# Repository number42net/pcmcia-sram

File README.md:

# PCMCIA SRAM board

This board is primarily designed for use in the Amstrad NC-100 and NC-200 portable computers, but will likely work in other computers as well.

## Specifications:
+ 1024K * 8 bits static RAM
+ CR2032 backup battery
+ Long battery life expected, but not yet tested

## Potential issues
+ This project has not yet been fully tested! **Build it at your own risk!**
+ Will likely not work in computers that expect a 16bit card, but this hasn't been tested
+ Currently no write protect switch

## Design
+ This product is Open Source, licensed under [CERN-OHL-P v2](https://ohwr.org/cern_ohl_p_v2.txt)
+ The schematics and PCB designs have been produced with KiCAD 6.0

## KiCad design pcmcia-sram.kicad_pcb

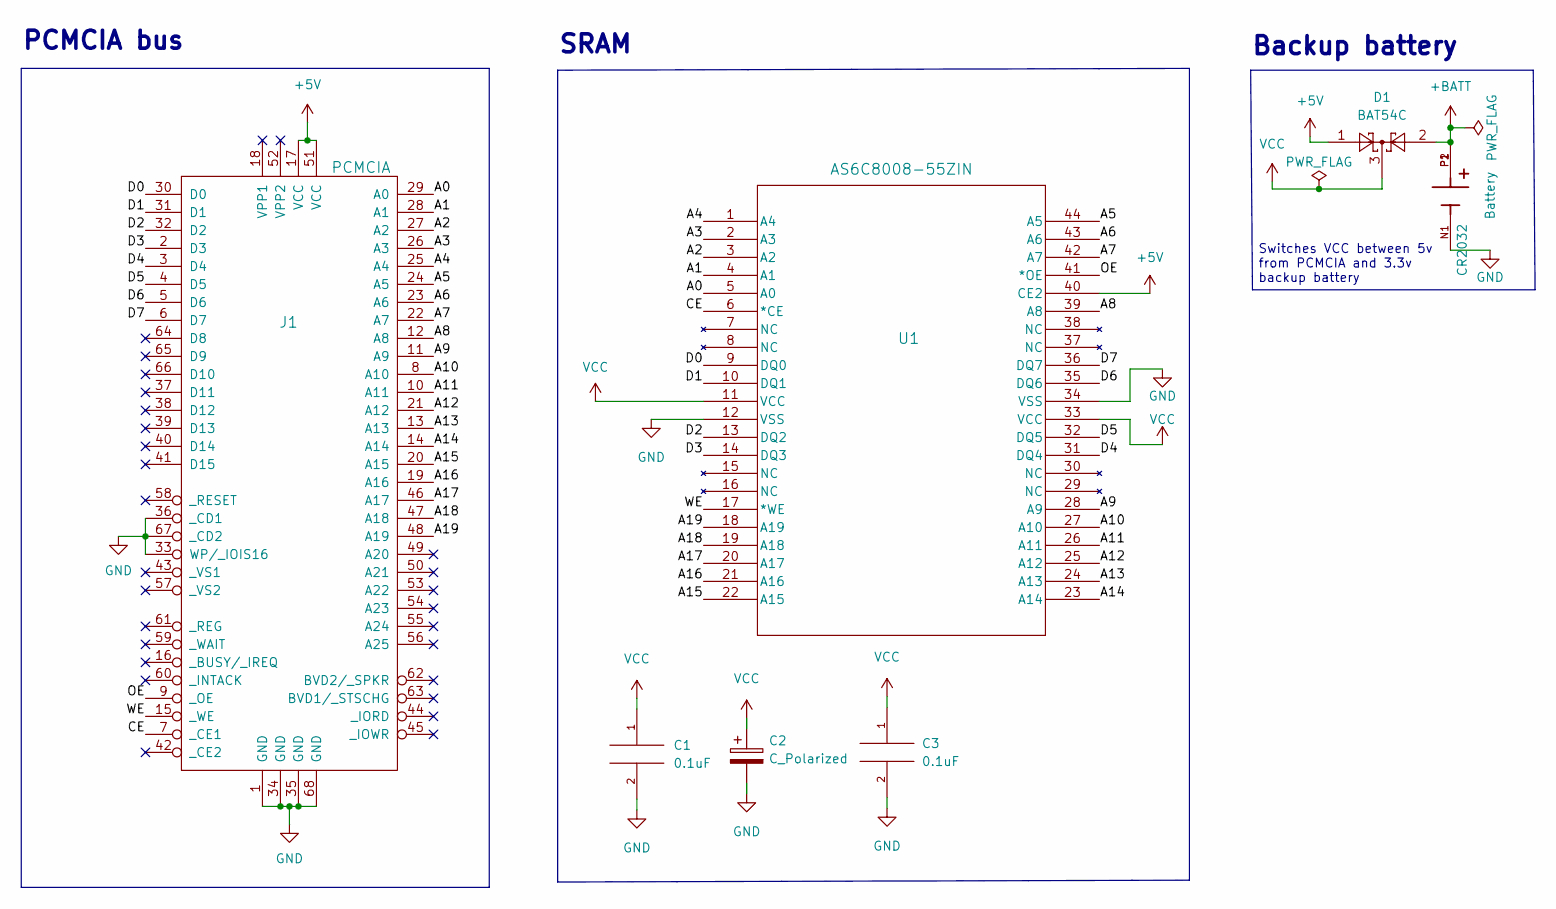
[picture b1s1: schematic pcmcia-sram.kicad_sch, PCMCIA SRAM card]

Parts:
C1, C3: 0.1uF; C_0805_2012Metric_Pad1.18x1.45mm_HandSolder
C2: C_Polarized; C_1206_3216Metric_Pad1.33x1.80mm_HandSolder
CR2032: Battery; BAT_BAT-HLD-001
D1: BAT54C; SOT-23
J1: PCMCIA; pcmcia
U1: AS6C8008-55ZIN; TSOP-II-44_10.16x18.41mm_P0.8mm

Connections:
+5V: D1.1, J1.17 (VCC), J1.51 (VCC), U1.40 (CE2)
+BATT: CR2032.P1, CR2032.P2, D1.2
/A0: J1.29 (A0), U1.5 (A0)
/A1: J1.28 (A1), U1.4 (A1)
/A2: J1.27 (A2), U1.3 (A2)
/A3: J1.26 (A3), U1.2 (A3)
/A4: J1.25 (A4), U1.1 (A4)
/A5: J1.24 (A5), U1.44 (A5)
/A6: J1.23 (A6), U1.43 (A6)
/A7: J1.22 (A7), U1.42 (A7)
/A8: J1.12 (A8), U1.39 (A8)
/A9: J1.11 (A9), U1.28 (A9)
/A10: J1.8 (A10), U1.27 (A10)
/A11: J1.10 (A11), U1.26 (A11)
/A12: J1.21 (A12), U1.25 (A12)
/A13: J1.13 (A13), U1.24 (A13)
/A14: J1.14 (A14), U1.23 (A14)
/A15: J1.20 (A15), U1.22 (A15)
/A16: J1.19 (A16), U1.21 (A16)
/A17: J1.46 (A17), U1.20 (A17)
/A18: J1.47 (A18), U1.19 (A18)
/A19: J1.48 (A19), U1.18 (A19)
/CE: J1.7 (_CE1), U1.6 (*CE)
/D0: J1.30 (D0), U1.9 (DQ0)
/D1: J1.31 (D1), U1.10 (DQ1)
/D2: J1.32 (D2), U1.13 (DQ2)
/D3: J1.2 (D3), U1.14 (DQ3)
/D4: J1.3 (D4), U1.31 (DQ4)
/D5: J1.4 (D5), U1.32 (DQ5)
/D6: J1.5 (D6), U1.35 (DQ6)
/D7: J1.6 (D7), U1.36 (DQ7)
/OE: J1.9 (_OE), U1.41 (*OE)
/WE: J1.15 (_WE), U1.17 (*WE)
GND: C1.2, C2.2, C3.2, CR2032.N1, J1.1 (GND), J1.33 (WP/_IOIS16), J1.34 (GND), J1.35 (GND), J1.36 (_CD1), J1.67 (_CD2), J1.68 (GND), U1.12 (VSS), U1.34 (VSS)
VCC: C1.1, C2.1, C3.1, D1.3, U1.11 (VCC), U1.33 (VCC)

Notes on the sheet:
Backup battery
Switches VCC between 5v from PCMCIA and 3.3v backup battery
PCMCIA bus
SRAM

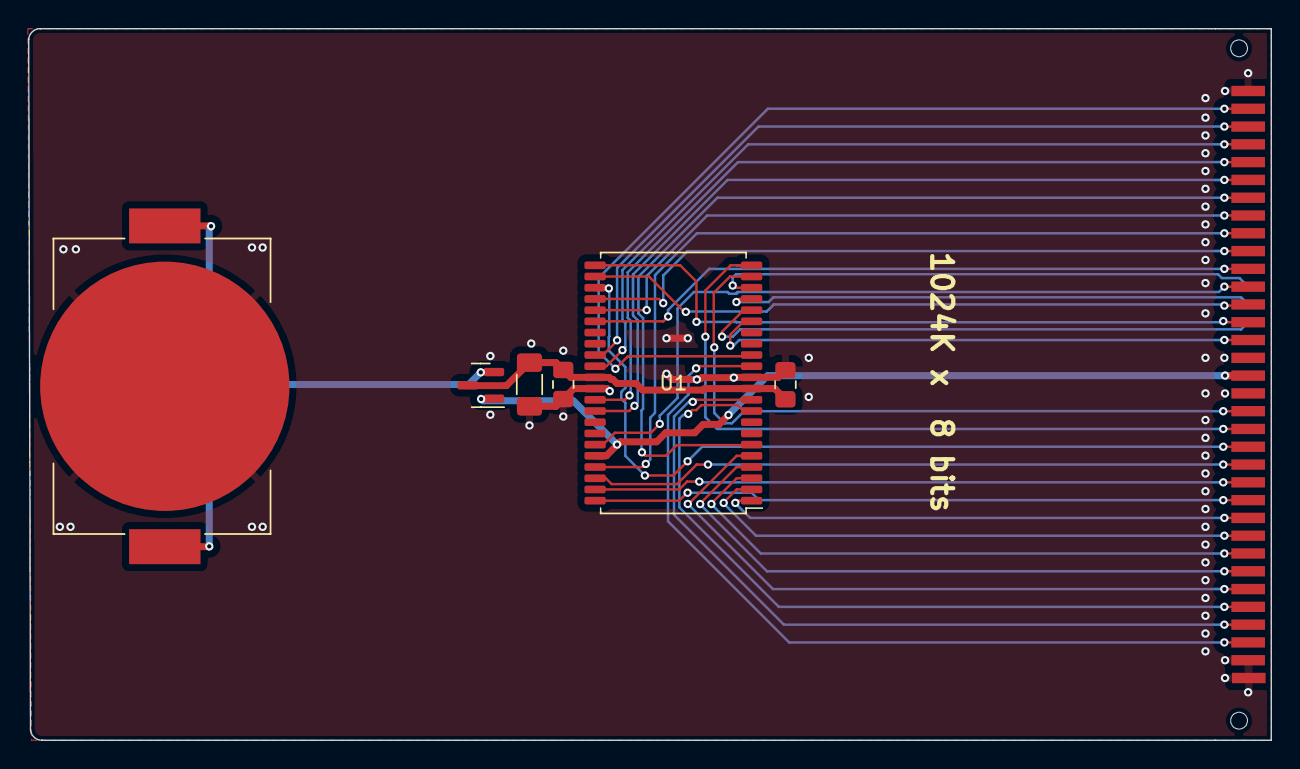
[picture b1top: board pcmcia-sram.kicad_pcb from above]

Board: 2 copper layers, 88.7 x 50.8 mm, 7 parts (0 on the bottom side), 35 nets.

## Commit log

2023-12-10 Copy of pcmcia-breakout
2023-12-10 Schematic done
2023-12-10 Initial layout
2023-12-10 Fixed address pin
2023-12-10 Various fixes
2023-12-11 Add License and Readme
2023-12-11 Add KiCad version
2023-12-23 Add new design
2023-12-23 Revision 1.1
